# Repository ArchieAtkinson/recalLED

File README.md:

# recalLED

recalLED is a hand held PCB Simon Says Game. The PCB has four different coloured LEDs and four buttons. Each round a sequence of lights will flash. Once the sequence is over you must use the buttons to input sequence back. If you get it right the green LED flashes and you go to the next level which increase the number of flashes in a sequences. If you lose the red LED will flash and you will go back to the beginning. The game remembers your score and flashes the number of levels you have won when you turn it on. For more information, see the article I wrote about its creation on [my website](https://www.archieatkinson.com/recalled).

This repo contains the Eagle PCB and Schematic Files, Soildworks files for a case and the firmware. The firmware is written using the Arduino IDE and can be uploaded to the MCU using an Arduino as a programmer. It runs off a single CR2032 battery.

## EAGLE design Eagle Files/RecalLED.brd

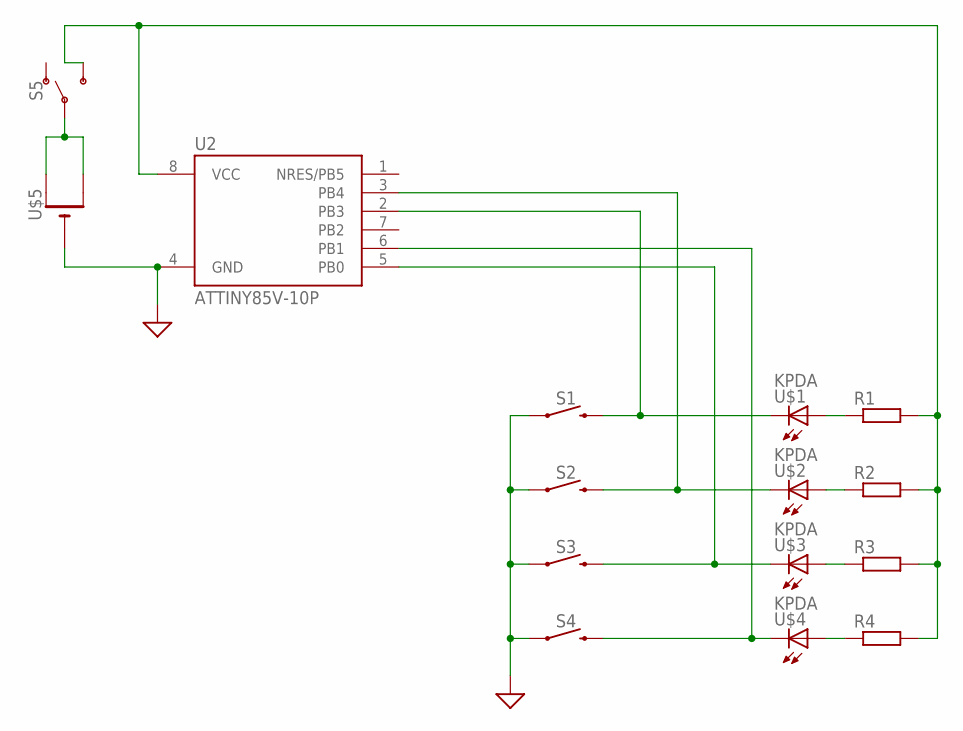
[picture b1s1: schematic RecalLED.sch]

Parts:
R1, R2, R3, R4: R-EU_M0805; M0805
S1, S2, S3, S4: MOMENTARY-SWITCH-SPST-SMD-6.2MM-TALL; TACTILE_SWITCH_SMD_6.2MM_TALL
S5: SWITCH-SPDT-SMD-RIGHT-ANGLE; SWITCH_SPST_SMD_A
U2: ATTINY85V-10P; PDIP08_300MIL
U$1, U$2, U$3, U$4: KPDA
U$5: CR2032SMT; CR2032-SMD

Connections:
GND: S1.A2 (1), S2.A2 (1), S3.A2 (1), S4.A2 (1), U2.4 (GND), U$5.-
unnamed: S1.B2 (2), U2.2 (PB3), U$1.P$2 (C)
unnamed: S2.B2 (2), U2.3 (PB4), U$2.P$2 (C)
unnamed: S3.B2 (2), U2.5 (PB0), U$3.P$2 (C)
unnamed: S4.B2 (2), U2.6 (PB1), U$4.P$2 (C)
unnamed: R4.1, U$4.P$1 (A)
unnamed: R3.1, U$3.P$1 (A)
unnamed: R2.1, U$2.P$1 (A)
unnamed: R1.1, U$1.P$1 (A)
unnamed: S5.2, U$5.+$1 (+), U$5.+$2 (+1)
unnamed: R1.2, R2.2, R3.2, R4.2, S5.3 (S), U2.8 (VCC)

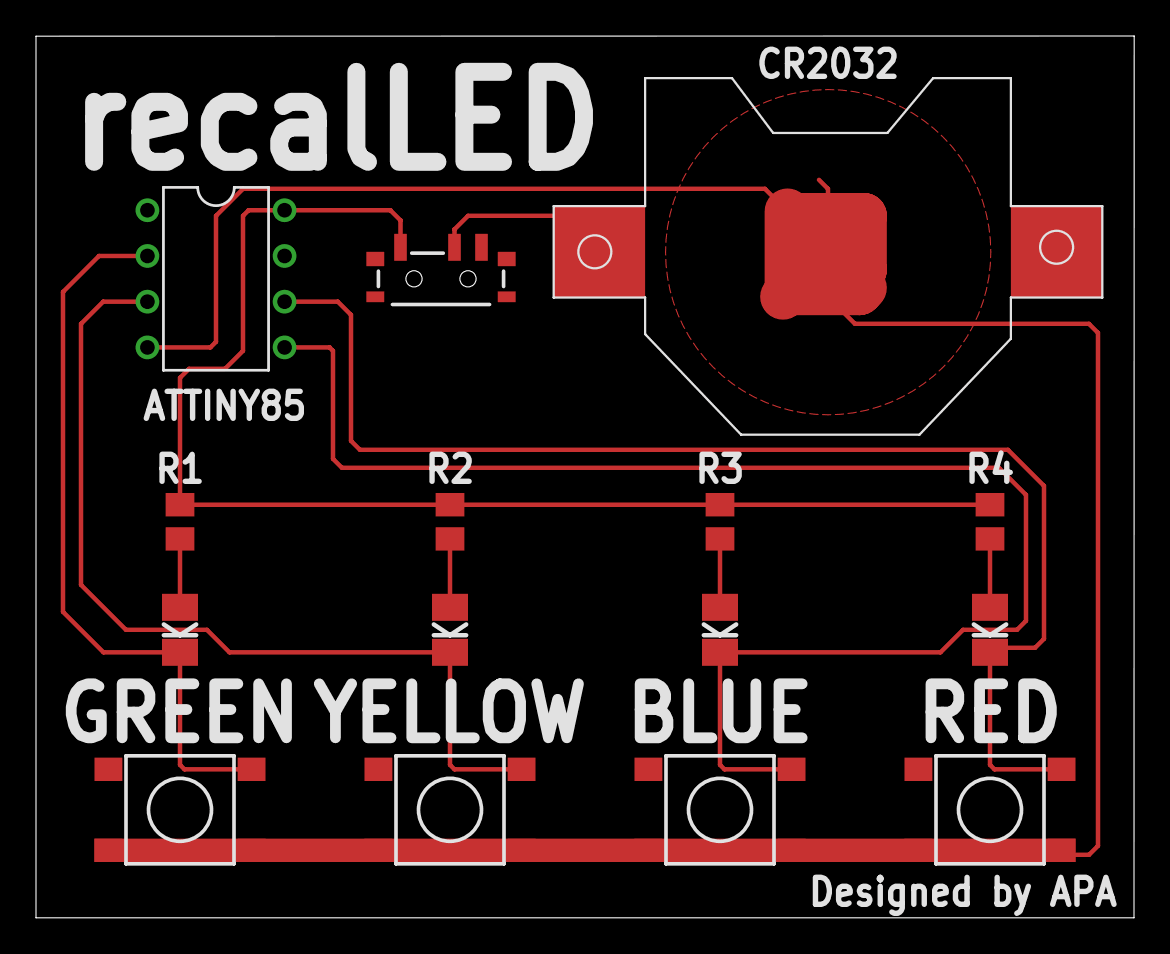
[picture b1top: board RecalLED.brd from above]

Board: 2 copper layers, 61.0 x 49.0 mm, 15 parts (0 on the bottom side), 11 nets.

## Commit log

2019-04-15 Remade Repositories

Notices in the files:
parts and their libraries:
SparkFun-Switches: Licensing: Creative Commons ShareAlike 4.0 International - https://creativecommons.org/licenses/by-sa/4.0
